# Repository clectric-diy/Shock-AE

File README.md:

# Shock-AE
A barebones version of our Spark-AE designed to fit in 1U instead of 2U.

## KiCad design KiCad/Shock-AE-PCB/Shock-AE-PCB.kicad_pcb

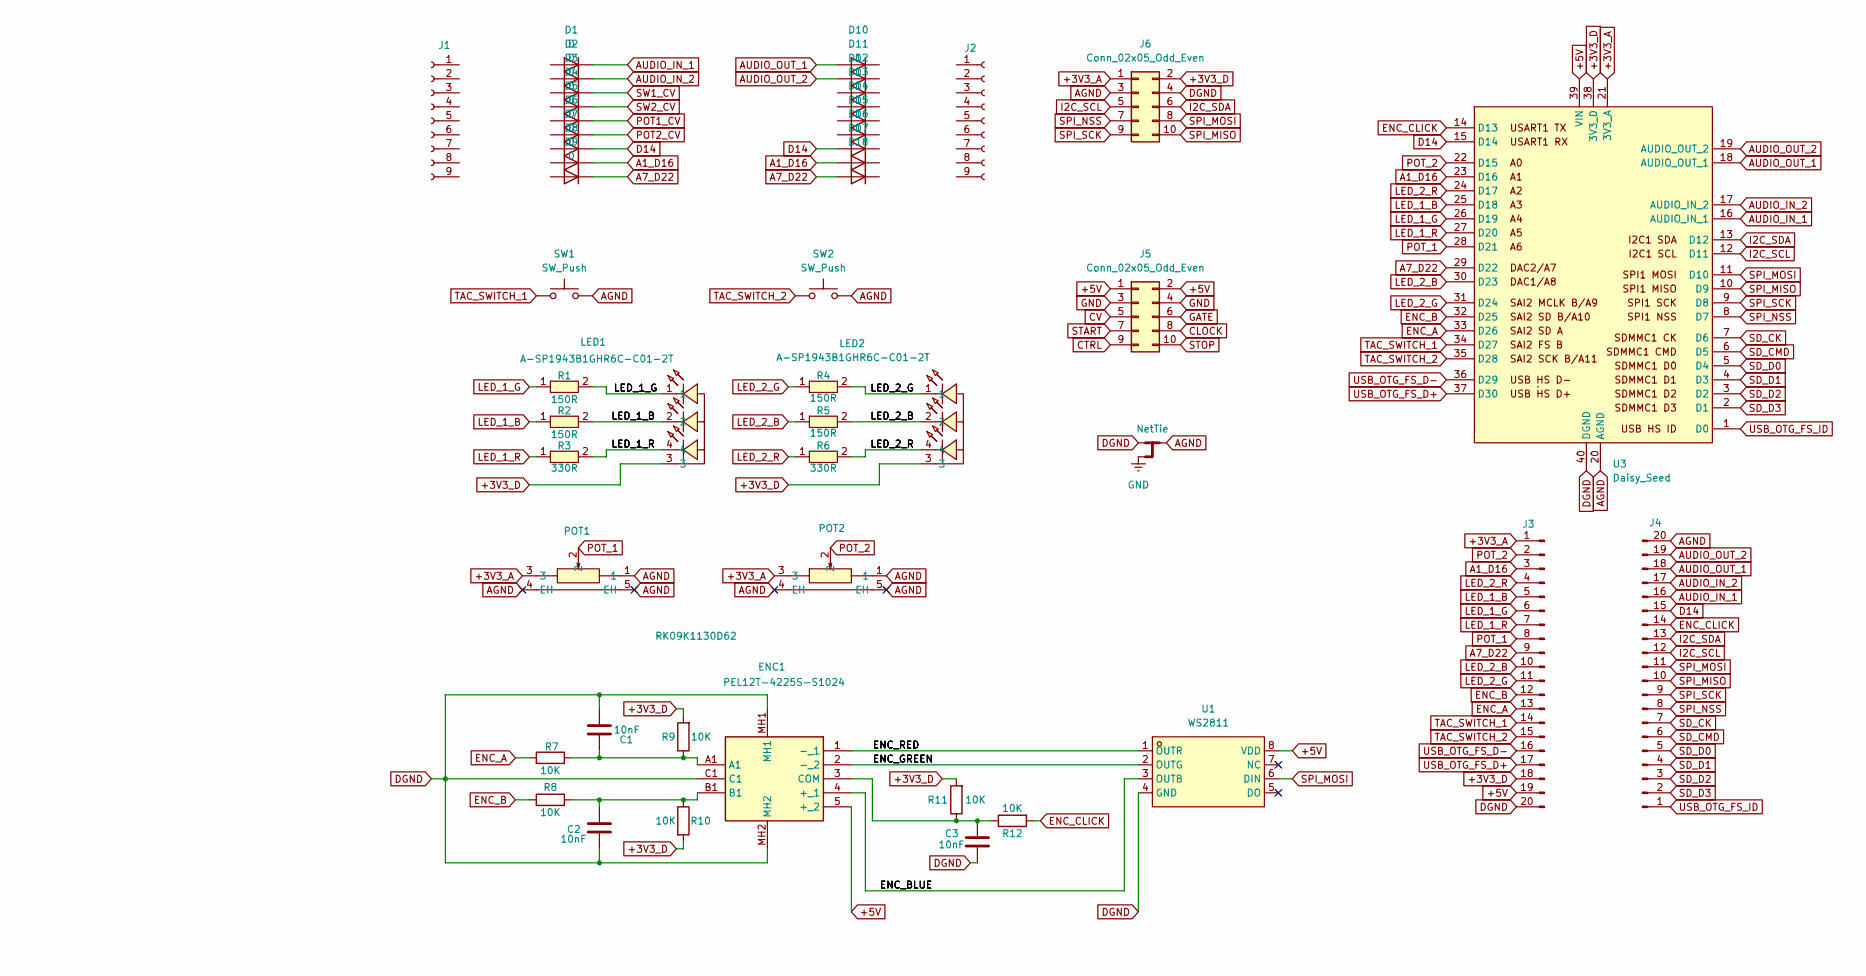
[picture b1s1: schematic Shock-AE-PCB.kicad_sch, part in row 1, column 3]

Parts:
C1, C2, C3: 10nF; C_0402_1005Metric
D1, D2, D3, D4, D5, D6, D7, D8, D9, D10, D11, D12, D13, D14, D15, D16, D17, D18: D; D_0402_1005Metric
ENC1: PEL12T-4225S-S1024; PEL12T4225SS1024; Mouser Part Number 652-PEL12T4225SS1024
J1, J2: Conn_01x09_Socket; PinSocket_1x09_P2.54mm_Vertical
J3, J4: Conn_01x20_Pin; Connector_PinSocket-1x20-P2.54mm_Mill-Max_315-13-120-41-004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
J5, J6: Conn_02x05_Odd_Even; PinHeader_2x05_P2.54mm_Vertical
LED1, LED2: A-SP1943B1GHR6C-C01-2T; LED-SMD_4P-L1.6-W1.5-BL_A-SP1943B1GHR6C-C01-2T; LCSC Part C19171342
NT1: NetTie; NetTie-3_SMD_Pad0.5mm
POT1, POT2: RK09K1130D62; LCSC Part C470399
R1, R2, R4, R5: 150R; R_0402_1005Metric
R3, R6: 330R; R_0402_1005Metric
R7, R8, R9, R10, R11, R12: 10K; R_0402_1005Metric
SW1, SW2: SW_Push; SW_PUSH_6mm
U1: WS2811; SOP-8_L4.9-W3.9-P1.27-LS6.0-BL; LCSC Part C114581
U3: Daisy_Seed; DAISY_SEED

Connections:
+3V3_A: J3.1, J6.1, POT1.3, POT2.3, U3.21 (3V3_A)
+3V3_D: J3.18, J6.2, LED1.3, LED2.3, R9.2, R10.2, R11.2, U3.38 (3V3_D)
+5V: ENC1.5 (+_2), J3.19, J5.1, J5.2, U1.8 (VDD), U3.39 (VIN)
A1_D16: D8.1 (K), D17.2 (A), J3.3, U3.23 (D16)
A7_D22: D9.1 (K), D18.2 (A), J3.9, U3.29 (D22)
AGND: J4.20, J6.3, NT1.2, POT1.1, POT1.4 (EH), POT1.5 (EH), POT2.1, POT2.4 (EH), POT2.5 (EH), SW1.2, SW2.2, U3.20 (AGND)
AUDIO_IN_1: D1.1 (K), J4.16, U3.16 (AUDIO_IN_1)
AUDIO_IN_2: D2.1 (K), J4.17, U3.17 (AUDIO_IN_2)
AUDIO_OUT_1: D10.2 (A), J4.18, U3.18 (AUDIO_OUT_1)
AUDIO_OUT_2: D11.2 (A), J4.19, U3.19 (AUDIO_OUT_2)
CLOCK: J5.8
CTRL: J5.9
CV: J5.5
D14: D7.1 (K), D16.2 (A), J4.15, U3.15 (D14)
DGND: C1.2, C2.2, C3.2, ENC1.C1, ENC1.MH1, ENC1.MH2, J3.20, J6.4, NT1.1, U1.4 (GND), U3.40 (DGND)
ENC_A: J3.13, R7.2, U3.33 (D26)
ENC_B: J3.12, R8.2, U3.32 (D25)
ENC_CLICK: J4.14, R12.2, U3.14 (D13)
GATE: J5.6
GND: J5.3, J5.4, NT1.3
I2C_SCL: J4.12, J6.5, U3.12 (D11)
I2C_SDA: J4.13, J6.6, U3.13 (D12)
LED_1_B: J3.5, R2.1, U3.25 (D18)
LED_1_G: J3.6, R1.1, U3.26 (D19)
LED_1_R: J3.7, R3.1, U3.27 (D20)
LED_2_B: J3.10, R5.1, U3.30 (D23)
LED_2_G: J3.11, R4.1, U3.31 (D24)
LED_2_R: J3.4, R6.1, U3.24 (D17)
unnamed: C1.1, ENC1.A1, R7.1, R9.1
unnamed: C2.1, ENC1.B1, R8.1, R10.1
unnamed: ENC1.4 (+_1), U1.3 (OUTB)
unnamed: ENC1.1 (-_1), U1.1 (OUTR)
unnamed: ENC1.2 (-_2), U1.2 (OUTG)
unnamed: C3.1, ENC1.3 (COM), R11.1, R12.1
unnamed: LED1.1, R1.2
unnamed: LED1.2, R2.2
unnamed: LED1.4, R3.2
unnamed: LED2.1, R4.2
unnamed: LED2.2, R5.2
unnamed: LED2.4, R6.2
POT1_CV: D5.1 (K)
POT2_CV: D6.1 (K)
POT_1: J3.8, POT1.2, U3.28 (D21)
POT_2: J3.2, POT2.2, U3.22 (D15)
SD_CK: J4.7, U3.7 (D6)
SD_CMD: J4.6, U3.6 (D5)
SD_D0: J4.5, U3.5 (D4)
SD_D1: J4.4, U3.4 (D3)
SD_D2: J4.3, U3.3 (D2)
SD_D3: J4.2, U3.2 (D1)
SPI_MISO: J4.10, J6.10, U3.10 (D9)
SPI_MOSI: J4.11, J6.8, U1.6 (DIN), U3.11 (D10)
SPI_NSS: J4.8, J6.7, U3.8 (D7)
SPI_SCK: J4.9, J6.9, U3.9 (D8)
START: J5.7
STOP: J5.10
SW1_CV: D3.1 (K)
SW2_CV: D4.1 (K)
TAC_SWITCH_1: J3.14, SW1.1, U3.34 (D27)
TAC_SWITCH_2: J3.15, SW2.1, U3.35 (D28)
USB_OTG_FS_D+: J3.17, U3.37 (D30)
USB_OTG_FS_D-: J3.16, U3.36 (D29)
USB_OTG_FS_ID: J4.1, U3.1 (D0)

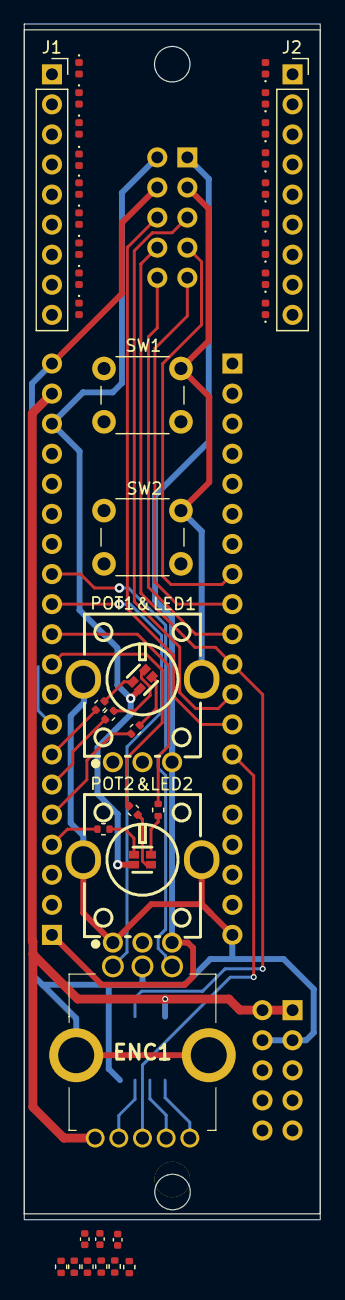
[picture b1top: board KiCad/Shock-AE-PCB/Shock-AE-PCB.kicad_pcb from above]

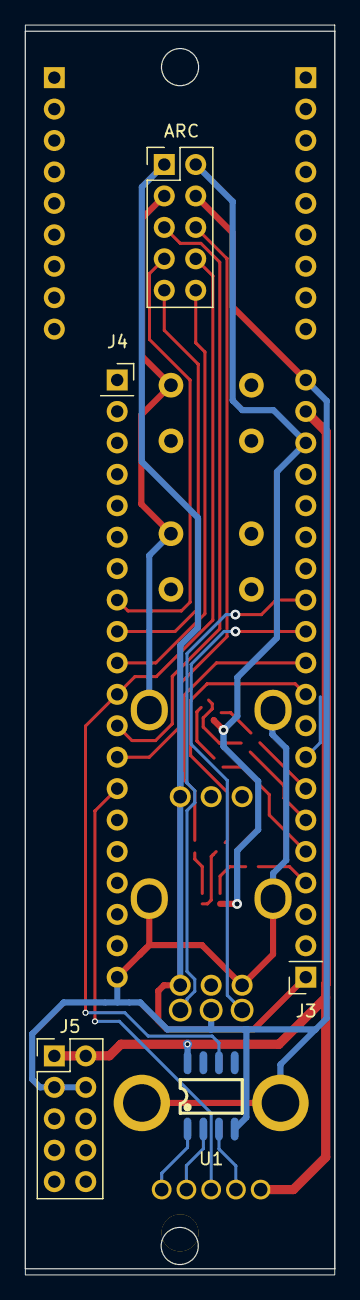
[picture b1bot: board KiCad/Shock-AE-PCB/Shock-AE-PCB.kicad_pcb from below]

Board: 2 copper layers, 25.0 x 101.0 mm, 48 parts (6 on the bottom side), 44 nets.

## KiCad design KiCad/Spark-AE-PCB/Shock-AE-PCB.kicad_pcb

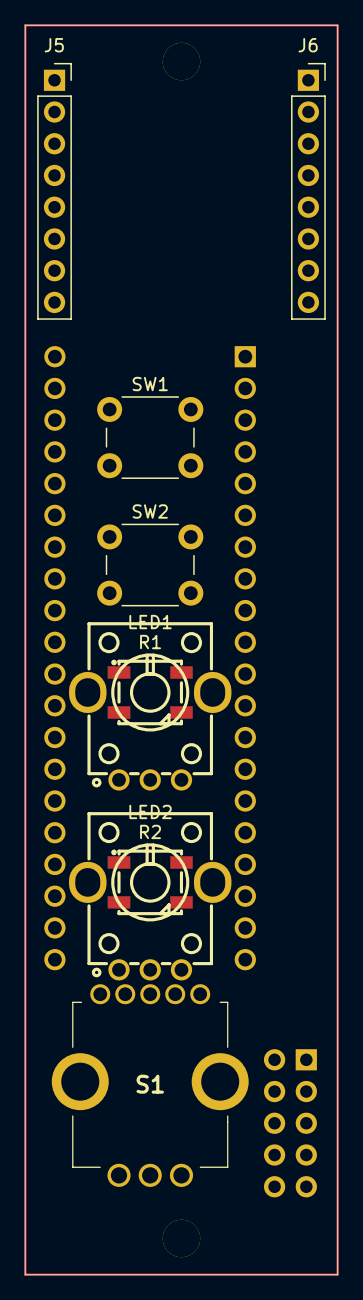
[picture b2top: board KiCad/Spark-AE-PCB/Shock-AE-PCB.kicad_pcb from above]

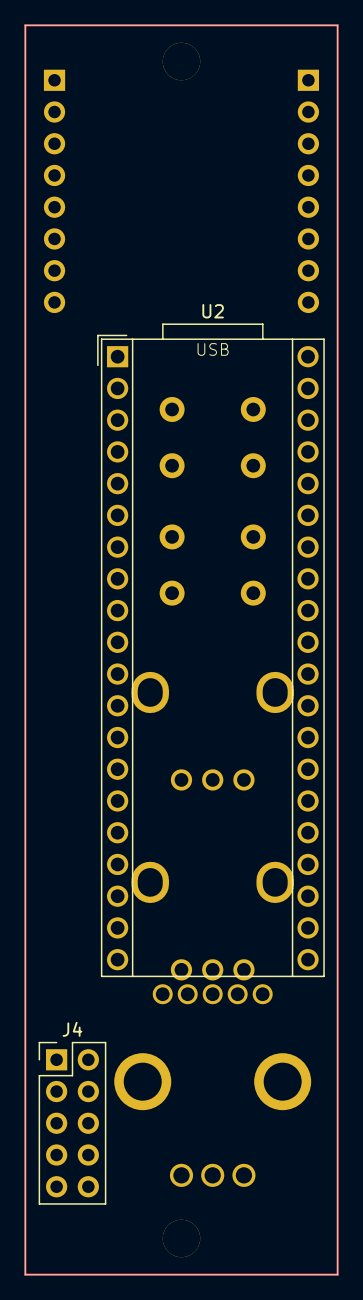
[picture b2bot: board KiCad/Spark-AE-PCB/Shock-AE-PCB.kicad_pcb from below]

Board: 2 copper layers, 25.0 x 100.0 mm, 11 parts (2 on the bottom side), 6 nets, no tracks yet.

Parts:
J4: Conn_02x05_Odd_Even; PinHeader_2x05_P2.54mm_Vertical
J5, J6: Conn_01x08_Socket; PinSocket_1x08_P2.54mm_Vertical
LED1, LED2: WS2812B-V5/W; LED-SMD_4P-L5.0-W5.0-TL-1
R1, R2: RK09K1130A8G; RES-TH_RK09K113004U
S1: PEL12T-4225S-S1024; PEL12T4225SS1024
SW1, SW2: SW_Push; SW_PUSH_6mm
U2: Daisy_Seed; DAISY_SEED

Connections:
+5V: J4.1, J4.2
AUDIO_IN_1: J5.1, U2.16 (AUDIO_IN_1)
AUDIO_IN_2: J5.2, U2.17 (AUDIO_IN_2)
AUDIO_OUT_1: J6.1, U2.18 (AUDIO_OUT_1)
AUDIO_OUT_2: J6.2, U2.19 (AUDIO_OUT_2)
GND: J4.3, J4.4, U2.20 (AGND), U2.40 (DGND)

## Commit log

2026-02-01 reclaiming the Shock name to use as smaller module
2026-02-01 update of title and description in config file to repurpose Shock name
2026-02-01 removing old Shock-EU files to repurpose the Shock name
2026-02-01 committing Spark-AE files to be reduced to Shock-AE
2026-02-01 renamed all to be Shock-AE
2026-02-03 rearranged Shock controls to be aligned and offset with bus connector
2026-02-28 ignoring fabrication production files
2026-02-28 placed remaining components and roughed in the traces
2026-02-28 ignoring KiCad working files
2026-02-28 using design rule checks from Cimos/KiCad-CustomDesignRules
2026-02-28 retracing to seperate analog and digital gnd
2026-03-01 partiallly retraced. time for bed.
2026-03-09 as expected, AE-1U is too small to squeeze a full Daisy Pod clone (see desc)
    This will be the final commit of an attempt to squeeze the full clone onto the AE-1U "Shock". I am moving now to make it an AE-2U called the "Spark".
    I plan to come back around to make the "Shock" a slimmed down version of the "Spark" in an AE-1U size.

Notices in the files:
KiCad/Shock-AE-PCB/Shock-AE-PCB.kicad_pcb:
Copyright © 2026 clectric.diy Licensed under CERN-OHL-S v2
